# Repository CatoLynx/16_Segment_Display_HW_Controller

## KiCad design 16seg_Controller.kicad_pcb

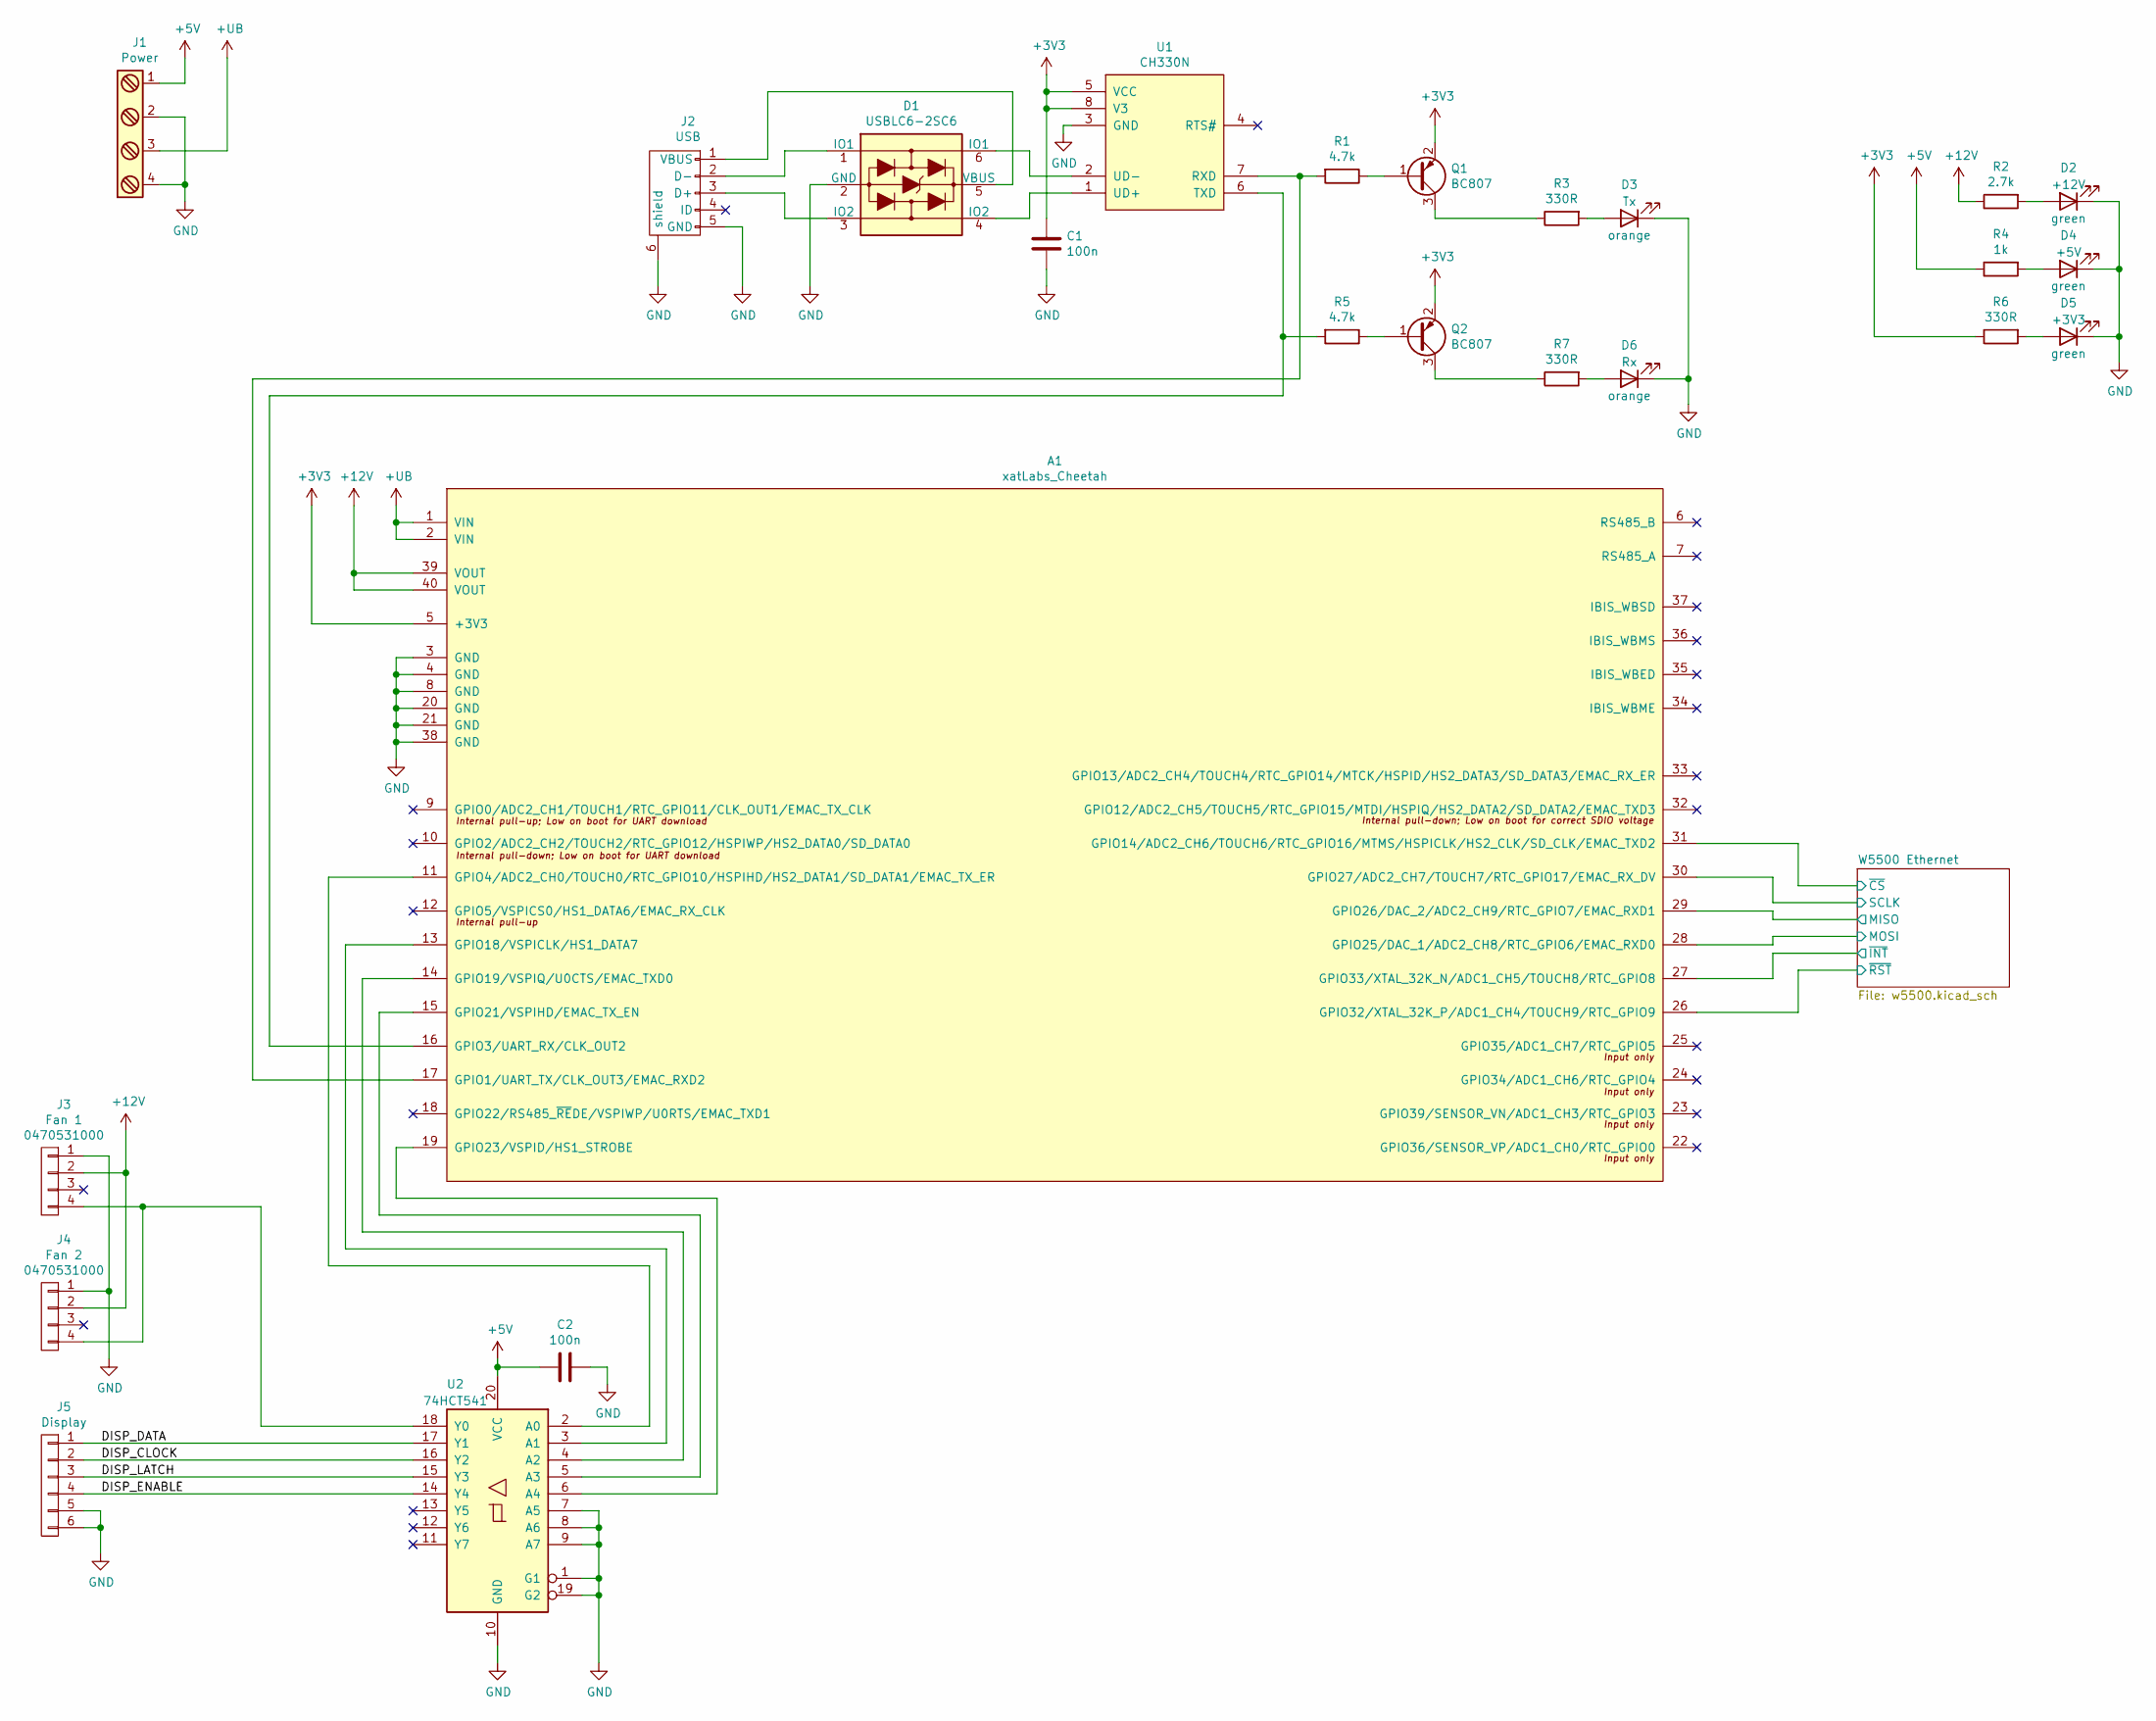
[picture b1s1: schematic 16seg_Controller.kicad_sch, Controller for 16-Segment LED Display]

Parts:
A1: xatLabs_Cheetah; xatLabs_Cheetah_SmallPads
C1, C2: 100n; C_0603
D1: USBLC6-2SC6; SOT-23-6
D2: +12V; LED_0603
D3: Tx; LED_0603
D4: +5V; LED_0603
D5: +3V3; LED_0603
D6: Rx; LED_0603
J1: Power; Terminal_Block_TE_282836-4
J2: USB; Mini_USB_THT_JST_UB-M5BR-DM14-4D
J3: Fan 1; Molex_0470531000
J4: Fan 2; Molex_0470531000
J5: Display; IDC_Header_Straight_6pins
Q1, Q2: BC807; SOT-23
R1, R5: 4.7k; R_0603
R2: 2.7k; R_0603
R3, R6, R7: 330R; R_0603
R4: 1k; R_0603
U1: CH330N; SOIC-8_3.9x4.9mm_Pitch1.27mm
U2: 74HCT541; SOIC-20W_7.5x12.8mm_Pitch1.27mm

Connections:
+3V3: A1.5 (+3V3), C1.1, Q1.2 (E), Q2.2 (E), R6.1, U1.5 (VCC), U1.8 (V3); also elsewhere on the board
+5V: C2.2, J1.1, R4.1, U2.20 (VCC)
+12V: A1.39 (VOUT), A1.40 (VOUT), J3.2, J4.2, R2.1
+UB: A1.1 (VIN), A1.2 (VIN), J1.3
/DISP_CLOCK: J5.2, U2.16 (Y2)
/DISP_DATA: J5.1, U2.17 (Y1)
/DISP_ENABLE: J5.4, U2.14 (Y4)
/DISP_LATCH: J5.3, U2.15 (Y3)
/W5500 Ethernet/MISO: A1.29 (GPIO26/DAC_2/ADC2_CH9/RTC_GPIO7/EMAC_RX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); also elsewhere on the board
/W5500 Ethernet/MOSI: A1.28 (GPIO25/DAC_1/ADC2_CH8/RTC_GPIO6/EMAC_RX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); also elsewhere on the board
/W5500 Ethernet/SCLK: A1.30 (GPIO27/ADC2_CH7/TOUCH7/RTC_GPIO17/EMAC_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); also elsewhere on the board
/W5500 Ethernet/~CS: A1.31 (GPIO14/ADC2_CH6/TOUCH6/RTC_GPIO16/MTMS/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); also elsewhere on the board
/W5500 Ethernet/~INT: A1.27 (GPIO33/XTAL_32K_N/ADC1_CH5/TOUCH8/RTC_G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); also elsewhere on the board
/W5500 Ethernet/~RST: A1.26 (GPIO32/XTAL_32K_P/ADC1_CH4/TOUCH9/RTC_G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); also elsewhere on the board
GND: A1.3 (GND), A1.4 (GND), A1.8 (GND), A1.20 (GND), A1.21 (GND), A1.38 (GND), C1.2, C2.1, D1.2 (GND), D2.1 (K), D3.1 (K), D4.1 (K), D5.1 (K), D6.1 (K), J1.2, J1.4, J2.5 (GND), J2.6 (shield), J3.1, J4.1, J5.5, J5.6, U1.3 (GND), U2.1 (G1), U2.7 (A5), U2.8 (A6), U2.9 (A7), U2.10 (GND), U2.19 (G2); also elsewhere on the board
unnamed: A1.11 (GPIO4/ADC2_CH0/TOUCH0/RTC_GPIO10/HSPIHD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), U2.2 (A0)
unnamed: A1.13 (GPIO18/VSPICLK/HS1_DATA7), U2.3 (A1)
unnamed: A1.14 (GPIO19/VSPIQ/U0CTS/EMAC_TXD0), U2.4 (A2)
unnamed: A1.15 (GPIO21/VSPIHD/EMAC_TX_EN), U2.5 (A3)
unnamed: A1.16 (GPIO3/UART_RX/CLK_OUT2), R5.2, U1.6 (TXD)
unnamed: A1.17 (GPIO1/UART_TX/CLK_OUT3/EMAC_RXD2), R1.2, U1.7 (RXD)
unnamed: A1.19 (GPIO23/VSPID/HS1_STROBE), U2.6 (A4)
unnamed: D1.1 (IO1), J2.2 (D-)
unnamed: D1.3 (IO2), J2.3 (D+)
unnamed: D1.4 (IO2), U1.1 (UD+)
unnamed: D1.5 (VBUS), J2.1 (VBUS)
unnamed: D1.6 (IO1), U1.2 (UD-)
unnamed: D2.2 (A), R2.2
unnamed: D3.2 (A), R3.2
unnamed: D4.2 (A), R4.2
unnamed: D5.2 (A), R6.2
unnamed: D6.2 (A), R7.2
unnamed: J3.4, J4.4, U2.18 (Y0)
unnamed: Q1.1 (B), R1.1
unnamed: Q1.3 (C), R3.1
unnamed: Q2.1 (B), R5.1
unnamed: Q2.3 (C), R7.1

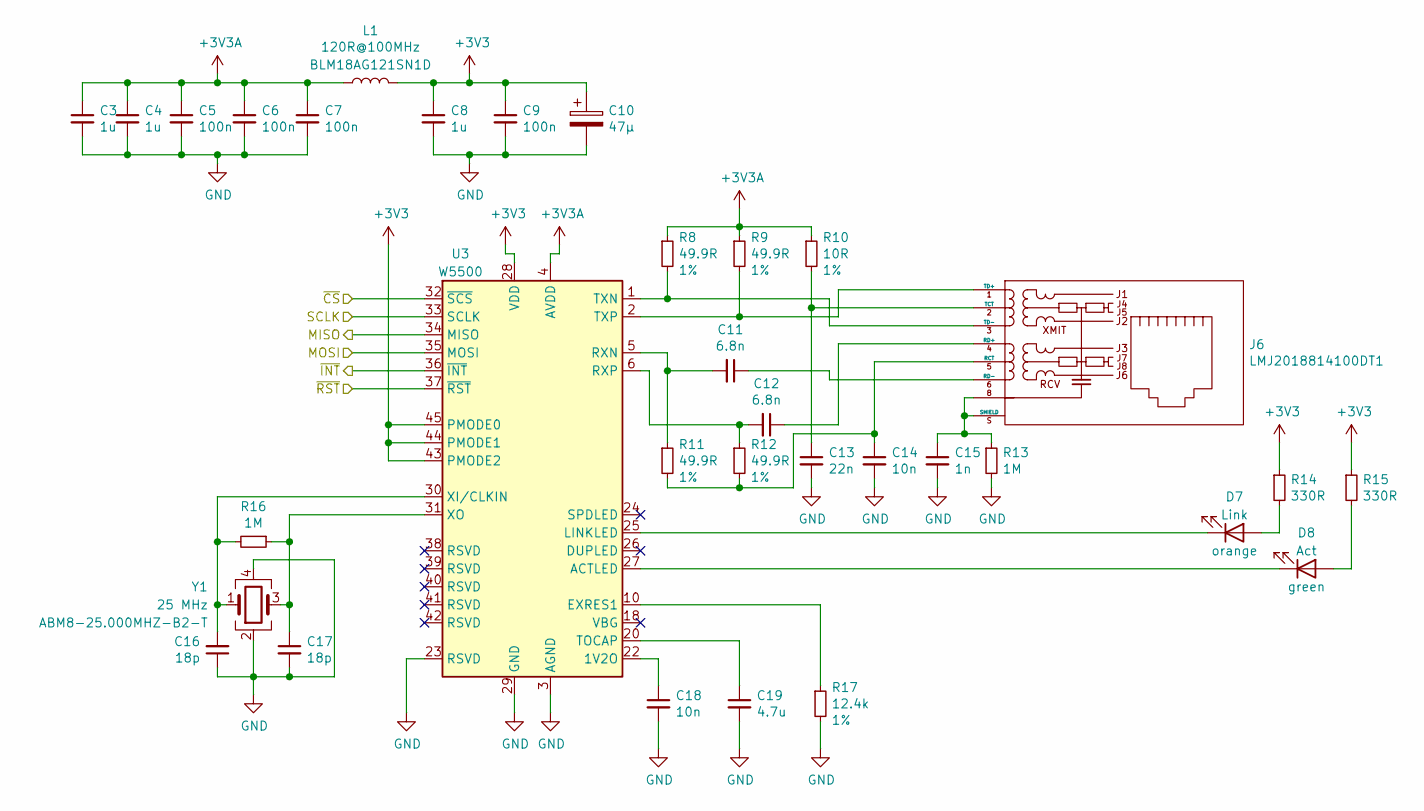
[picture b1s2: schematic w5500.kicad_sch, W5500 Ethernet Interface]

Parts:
C3, C4, C8: 1u; C_0805
C5, C6, C7, C9: 100n; C_0603
C10: 47µ; CP_Elec_5x5.8
C11, C12: 6.8n; C_0603
C13: 22n; C_0603
C14, C18: 10n; C_0603
C15: 1n; C_0603
C16, C17: 18p; C_0603
C19: 4.7u; C_0805
D7: Link; LED_0603
D8: Act; LED_0603
J6: LMJ2018814100DT1; Socket_RJ45_LMJ2018814100DT1
L1: 120R@100MHz; C_0603
R8, R9, R11, R12: 49.9R; R_0603
R10: 10R; R_0603
R13, R16: 1M; R_0603
R14, R15: 330R; R_0603
R17: 12.4k; R_0603
U3: W5500; LQFP-48_7x7mm_Pitch0.5mm
Y1: 25 MHz; Crystal_SMD_TXC_7M-4pin_3.2x2.5mm

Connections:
+3V3: C8.1, C9.1, C10.1, L1.2, R14.1, R15.1, U3.28 (VDD), U3.43 (PMODE2), U3.44 (PMODE1), U3.45 (PMODE0); also elsewhere on the board
+3V3A: C3.1, C4.1, C5.1, C6.1, C7.1, L1.1, R8.1, R9.1, R10.1, U3.4 (AVDD), U3.8 (AVDD), U3.11 (AVDD), U3.15 (AVDD), U3.17 (AVDD), U3.21 (AVDD)
/W5500 Ethernet/MISO: U3.34 (MISO); also elsewhere on the board
/W5500 Ethernet/MOSI: U3.35 (MOSI); also elsewhere on the board
/W5500 Ethernet/SCLK: U3.33 (SCLK); also elsewhere on the board
/W5500 Ethernet/~CS: U3.32 (~SCS); also elsewhere on the board
/W5500 Ethernet/~INT: U3.36 (~INT); also elsewhere on the board
/W5500 Ethernet/~RST: U3.37 (~RST); also elsewhere on the board
GND: C3.2, C4.2, C5.2, C6.2, C7.2, C8.2, C9.2, C10.2, C13.2, C14.2, C15.2, C16.1, C17.2, C18.2, C19.2, R13.2, R17.2, U3.3 (AGND), U3.9 (AGND), U3.14 (AGND), U3.16 (AGND), U3.19 (AGND), U3.23 (RSVD), U3.29 (GND), U3.48 (AGND), Y1.2, Y1.4; also elsewhere on the board
unnamed: C11.1, J6.6 (RD-)
unnamed: C11.2, R11.1, U3.5 (RXN)
unnamed: C12.1, J6.4 (RD+)
unnamed: C12.2, R12.1, U3.6 (RXP)
unnamed: C13.1, J6.2 (TCT), R10.2
unnamed: C14.1, J6.5 (RCT), R11.2, R12.2
unnamed: C15.1, J6.8, J6.S (SHIELD), R13.1
unnamed: C16.2, R16.2, U3.30 (XI/CLKIN), Y1.1
unnamed: C17.1, R16.1, U3.31 (XO), Y1.3
unnamed: C18.1, U3.22 (1V2O)
unnamed: C19.1, U3.20 (TOCAP)
unnamed: D7.1 (K), U3.25 (LINKLED)
unnamed: D7.2 (A), R14.2
unnamed: D8.1 (K), U3.27 (ACTLED)
unnamed: D8.2 (A), R15.2
unnamed: J6.1 (TD+), R9.2, U3.2 (TXP)
unnamed: J6.3 (TD-), R8.2, U3.1 (TXN)
unnamed: R17.1, U3.10 (EXRES1)

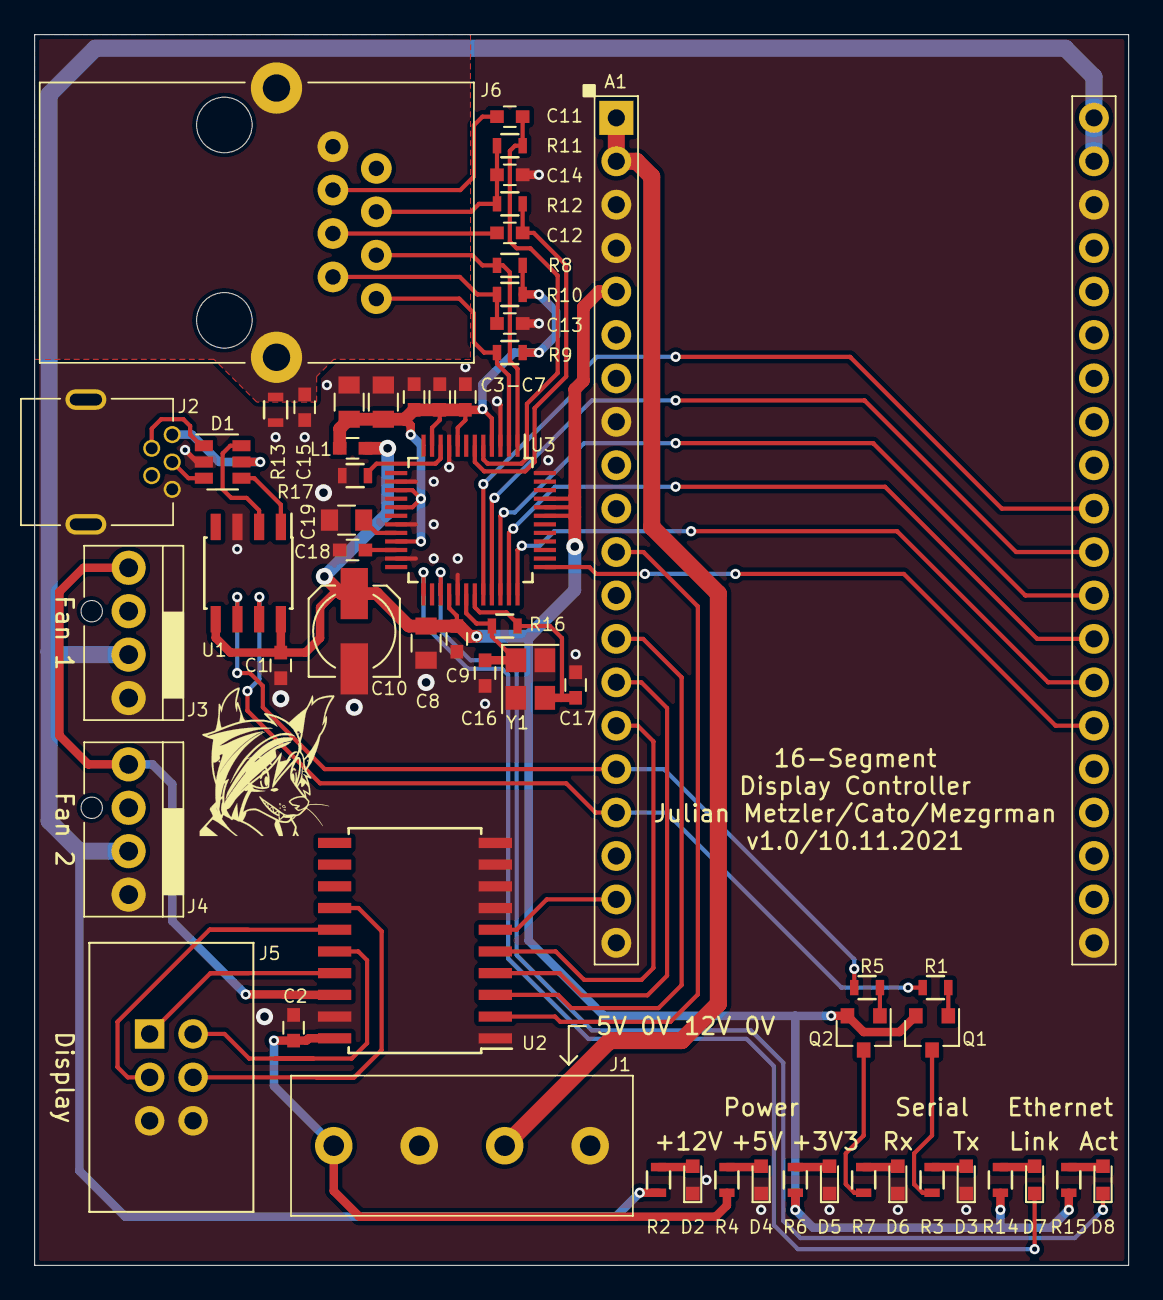
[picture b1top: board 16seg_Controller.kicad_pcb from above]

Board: 2 copper layers, 64.0 x 72.0 mm, 58 parts (0 on the bottom side), 56 nets.

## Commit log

2021-11-10 Add interactive BOM
2021-11-10 Fix missing paste on crystal pads
